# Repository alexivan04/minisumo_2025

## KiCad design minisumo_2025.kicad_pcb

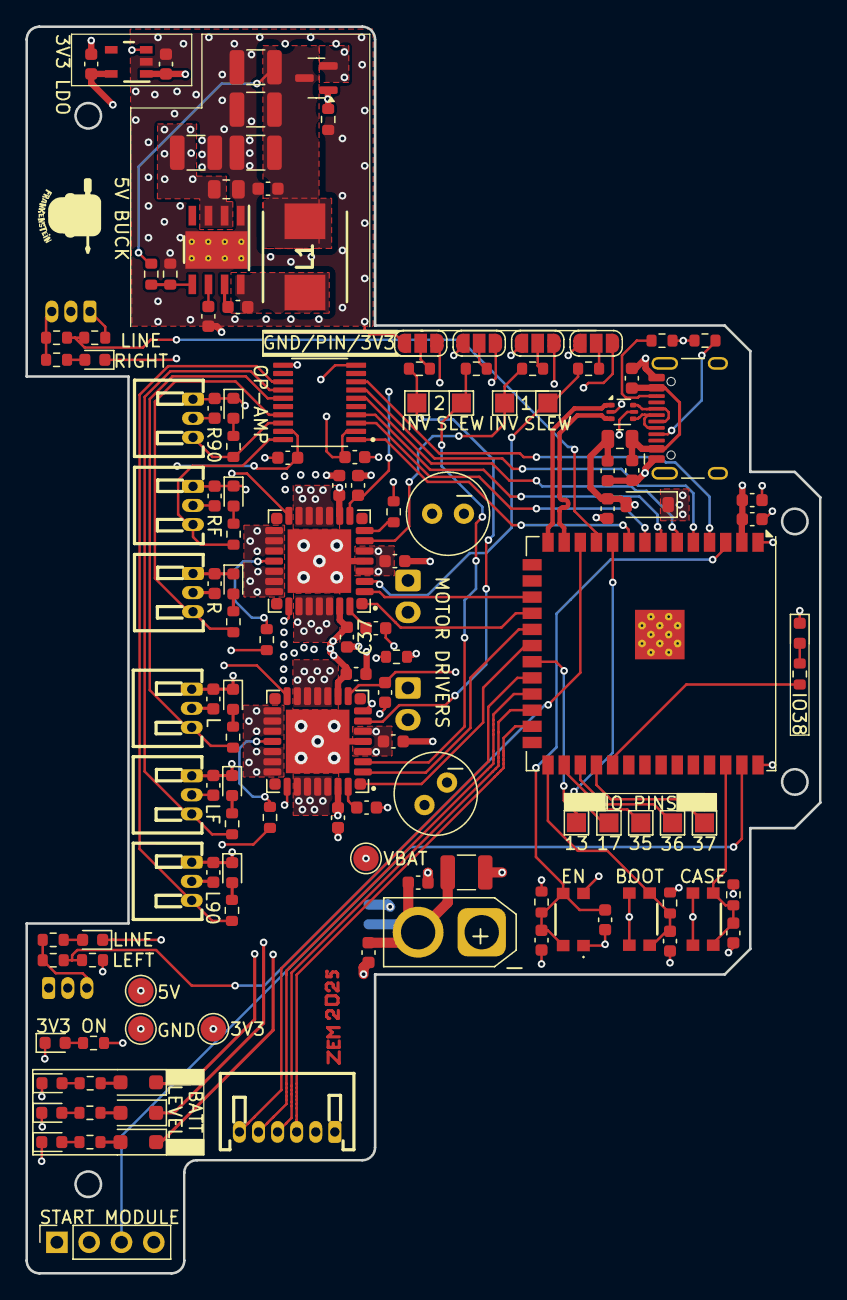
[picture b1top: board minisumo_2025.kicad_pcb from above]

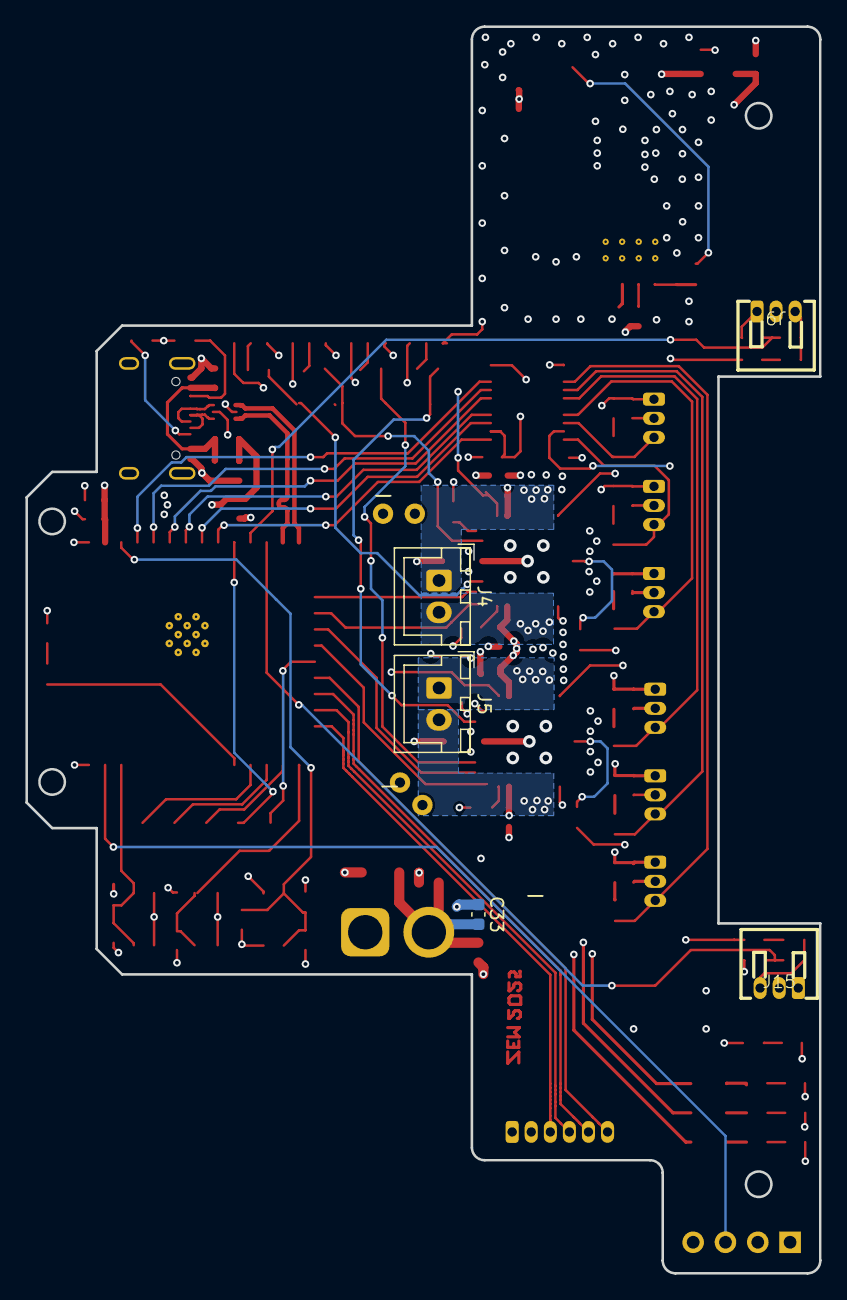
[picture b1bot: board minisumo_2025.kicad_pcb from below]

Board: 4 copper layers, 62.4 x 98.0 mm, 134 parts (5 on the bottom side), 85 nets.

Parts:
C1, C3, C6, C7, C11, C12, C16, C17, C18, C21, C23, C25, C26, C27, C28, C29, C30, C34, C37, C38, C44, C45, C46, C47, C48, C49: 0.1uF; C_0603_1608Metric
C2, C14, C15, C33: 10uF; C_0603_1608Metric
C4: 10uF; C_1210_3225Metric
C5: 220nF; C_0805_2012Metric
C8, C9, C10, C31: 47uF; C_1210_3225Metric
C13, C32, C36: 1uF; C_0603_1608Metric
C19, C20: 33nF; C_0603_1608Metric
C22, C24: 100uF - low ESR; C_Radial_D6.3mm_H11.0mm_P2.50mm
C35: 4.7uF; C_0603_1608Metric
D2, D7, D8, D9: 1.95Vf, 20mA, RED; LED_0603_1608Metric
D3: D_Schottky_Small; D_SOD-123
D4: 10V; D_SOD-123F
D5: 8.2V; D_SOD-123F
D6: 6.2V; D_SOD-123F
D10, D11, D12, D13, D14, D15, D16, D17, D18: LED_Small; LED_0603_1608Metric
FB1: FerriteBead_Small; C_0805_2012Metric
J1: USB_C Connector; USB_C_Receptacle_HCTL_HC-TYPE-C-16P-01A
J3: START_MODULE; PinSocket_1x04_P2.54mm_Vertical
J4: MOTOR1; JST_XH_B2B-XH-A_1x02_P2.50mm_Vertical
J5: MOTOR2; JST_XH_B2B-XH-A_1x02_P2.50mm_Vertical
J6: BATT_IN; AMASS_XT30U-F_1x02_P5.0mm_Vertical
J8: DISTANCE_CENTER; CONN-TH_S6B-ZR-3.4-LF-SN
J9: LINE_RIGHT; CONN-TH_S3B-ZR-3.4-LF-SN
J10: DISTANCE_R90; CONN-TH_S3B-ZR-3.4-LF-SN
J11: DISTANCE_R; CONN-TH_S3B-ZR-3.4-LF-SN
J12: DISTANCE_RF; CONN-TH_S3B-ZR-3.4-LF-SN
J13: DISTANCE_L90; CONN-TH_S3B-ZR-3.4-LF-SN
J14: DISTANCE_L; CONN-TH_S3B-ZR-3.4-LF-SN
J15: LINE_LEFT; CONN-TH_S3B-ZR-3.4-LF-SN
J16: DISTANCE_LF; CONN-TH_S3B-ZR-3.4-LF-SN
JP1, JP2, JP3, JP4: SolderJumper_3_Open; SolderJumper-3_P1.3mm_Open_RoundedPad1.0x1.5mm_NumberLabels
L1: 8.2uH, 21mOhm; INDPM7166X300N
Q1: Si2371EDS; SOT-23
R1, R6, R7, R8, R13, R14, R15, R16, R17, R18, R19, R25: 10k; R_0603_1608Metric
R2, R3: 5k1; R_0603_1608Metric
R4, R33: 100k; R_0603_1608Metric
R5: 24k9; R_0603_1608Metric
R9, R10, R11, R12, R21, R23: 1k; R_0603_1608Metric
R20, R26, R27, R28, R29, R30, R31, R32: 3k3; R_0603_1608Metric
R22, R24: 2k; R_0603_1608Metric
SW1: RESET; 435441019830
SW2: CASE; 435441019830
SW3: BOOT; 435441019830
TP1: GPIO13; TestPoint_Pad_1.5x1.5mm
TP6: SLEW_1; TestPoint_Pad_1.5x1.5mm
TP7: INV_1; TestPoint_Pad_1.5x1.5mm
TP8: GPIO35; TestPoint_Pad_1.5x1.5mm
TP9: GPIO36; TestPoint_Pad_1.5x1.5mm
TP10: SLEW_2; TestPoint_Pad_1.5x1.5mm
TP11: INV_2; TestPoint_Pad_1.5x1.5mm
TP12: GPIO37; TestPoint_Pad_1.5x1.5mm
TP13: GPIO17; TestPoint_Pad_1.5x1.5mm
U1: LMR33630ADDAR; DDA0008J
U2: USBLC6-2P6; SOT-666
U3: ESP32-S3-WROOM-1; ESP32-S3-WROOM-1U
U4: TLV75733PDBVR; DBV0005A_N
U5: TXS0108EPWR; SOP65P640X120-20N
U6, U7: MC33926PNB; QFN80P800X800X220-33N

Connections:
+3V3: C1.1, C2.1, C14.2, C27.1, C28.1, C29.1, J3.1, J8.1, JP1.3 (B), JP2.3 (B), JP3.3 (B), JP4.3 (B), R1.1, R6.1, R7.1, R8.1, R13.1, R15.1, U3.2 (3V3), U4.5 (OUT), U5.2 (VCCA), U5.10 (OE), U6.10 (EN), U6.16 (~D2), U7.10 (EN), U7.16 (~D2)
+5V: C15.2, C30.1, C44.1, C45.1, C46.1, C47.1, C48.1, C49.1, D3.1 (K), J9.2, J10.2, J11.2, J12.2, J13.2, J14.2, J15.2, J16.2, Q1.2 (S), U4.1 (IN), U4.3 (EN), U5.19 (VCCB)
+BATT: C4.1, C5.1, C19.1, C20.1, C21.1, C22.1, C23.1, C24.1, C25.1, C31.2, C33.2, C34.1, C35.2, C36.2, C37.1, C38.1, D4.1 (K), D5.1 (K), D6.1 (K), J6.2, U1.2 (VIN), U1.3 (EN), U6.4 (VPWR), U6.6 (VPWR), U6.11 (VPWR), U6.31 (VPWR), U7.4 (VPWR), U7.6 (VPWR), U7.11 (VPWR), U7.31 (VPWR)
/DRIVERS/CCP_1: C19.2, U6.32 (CCP)
/DRIVERS/CCP_2: C20.2, U7.32 (CCP)
/DRIVERS/INV_1: R11.1, TP7.1, U6.7 (INV)
/DRIVERS/INV_2: R12.1, TP11.1, U7.7 (INV)
/DRIVERS/MOTOR1_A: J4.1, U6.12 (OUT1), U6.13 (OUT1), U6.14 (OUT1), U6.15 (OUT1)
/DRIVERS/MOTOR1_B: J4.2, U6.27 (OUT2), U6.28 (OUT2), U6.29 (OUT2), U6.30 (OUT2)
/DRIVERS/MOTOR2_A: J5.1, U7.12 (OUT1), U7.13 (OUT1), U7.14 (OUT1), U7.15 (OUT1)
/DRIVERS/MOTOR2_B: J5.2, U7.27 (OUT2), U7.28 (OUT2), U7.29 (OUT2), U7.30 (OUT2)
/DRIVERS/SLEW_1: R9.1, TP6.1, U6.3 (SLEW)
/DRIVERS/SLEW_2: R10.1, TP10.1, U7.3 (SLEW)
/POWER/D_N: J1.A7 (D-), J1.B7 (D-), U2.4 (I/O2)
/POWER/D_P: J1.A6 (D+), J1.B6 (D+), U2.6 (I/O1)
/POWER/VBUS: C6.1, C26.1, D3.2 (A), FB1.2, Q1.1 (G), R33.1, U2.5 (VBUS)
/SENSORS/DISTANCE_L90_OUT: J13.3, R28.1, U5.13 (B7)
/SENSORS/DISTANCE_LF_OUT: J16.3, R30.1, U5.14 (B6)
/SENSORS/DISTANCE_L_OUT: J14.3, R29.1, U5.15 (B5)
/SENSORS/DISTANCE_R90_OUT: J10.3, R26.1, U5.18 (B2)
/SENSORS/DISTANCE_RF_OUT: J12.3, R27.1, U5.20 (B1)
/SENSORS/DISTANCE_R_OUT: J11.3, R20.1, U5.17 (B3)
/SENSORS/LINE_LEFT_OUT: J15.3, R23.2, R32.1
/SENSORS/LINE_RIGHT_OUT: J9.3, R21.2, R31.1
CASE: C18.1, R8.2, SW2.2 (D), SW2.3 (C), U3.38 (IO2)
D+: U2.1 (I/O1), U3.14 (USB_D+)
D-: U2.3 (I/O2), U3.13 (USB_D-)
DISTANCE_INTR: J8.6, U3.22 (IO14)
DISTANCE_L: U3.6 (IO6), U5.6 (A5)
DISTANCE_L90: U3.4 (IO4), U5.8 (A7)
DISTANCE_LF: U3.5 (IO5), U5.7 (A6)
DISTANCE_R: U3.7 (IO7), U5.4 (A3)
DISTANCE_R90: U3.8 (IO15), U5.3 (A2)
DISTANCE_RF: U3.9 (IO16), U5.1 (A1)
ESP_BOOT: C12.2, R7.2, SW3.2 (D), SW3.3 (C), U3.27 (IO0)
ESP_EN: C7.2, C32.2, R1.2, SW1.2 (D), SW1.3 (C), U3.3 (EN)
GND: C1.2, C2.2, C4.2, C5.2, C6.2, C7.1, C8.1, C9.1, C10.1, C11.1, C12.1, C13.2, C14.1, C15.1, C16.2, C17.2, C18.2, C21.2, C22.2, C23.2, C24.2, C25.2, C26.2, C27.2, C28.2, C29.2, C30.2, C31.1, C32.1, C33.1, C34.2, C35.1, C36.1, C37.2, C38.2, C44.2, C45.2, C46.2, C47.2, C48.2, C49.2, D2.1 (K), D7.1 (K), D8.1 (K), D9.1 (K), D10.1 (K), D11.1 (K), D12.1 (K), D13.1 (K), D14.1 (K), D15.1 (K), D16.1 (K), D17.1 (K), D18.1 (K), J1.A1 (GND), J1.A12 (GND), J1.B1 (GND), J1.B12 (GND), J3.2, J6.1, J8.2, J9.1, J10.1, J11.1, J12.1, J13.1, J14.1, J15.1, J16.1, JP1.1 (A), JP2.1 (A), JP3.1 (A), JP4.1 (A), R2.1, R3.1, R5.1, R14.1, R16.1, R22.1, R24.1, R33.2, SW1.1 (C), SW1.4 (C), SW2.1 (C), SW2.4 (C), SW3.1 (C), SW3.4 (C), U1.1 (PGND), U1.9 (AGND), U1.V, U2.2 (GND), U3.1 (GND), U3.40 (GND), U3.41 (GND), U4.2 (GND), U5.11 (GND), U6.5 (AGND), U6.18 (PGND), U6.19 (PGND), U6.20 (PGND), U6.22 (PGND), U6.23 (PGND), U6.24 (PGND), U6.26 (D1), U6.33 (AGND), U7.5 (AGND), U7.18 (PGND), U7.19 (PGND), U7.20 (PGND), U7.22 (PGND), U7.23 (PGND), U7.24 (PGND), U7.26 (D1), U7.33 (AGND)
GPIO1: J3.3, U3.39 (IO1)
GPIO8: R23.1, R24.2, U3.12 (IO8)
GPIO9: U3.17 (IO9), U6.2 (IN1)
GPIO10: U3.18 (IO10), U6.1 (IN2)
GPIO11: U3.19 (IO11), U7.2 (IN1)
GPIO12: U3.20 (IO12), U7.1 (IN2)
GPIO13: TP1.1, U3.21 (IO13)
GPIO17: TP13.1, U3.10 (IO17)
GPIO18: R21.1, R22.2, U3.11 (IO18)
GPIO21: J8.5, U3.23 (IO21)
GPIO35: TP8.1, U3.28 (IO35)
GPIO36: TP9.1, U3.29 (IO36)
GPIO37: TP12.1, U3.30 (IO37)
GPIO38: R19.1, U3.31 (IO38)
GPIO47: J8.4, U3.24 (IO47)
GPIO48: J8.3, U3.25 (IO48)
unnamed: C16.1, C17.1, FB1.1, J1.A4 (VBUS), J1.A9 (VBUS), J1.B4 (VBUS), J1.B9 (VBUS)
unnamed: D2.2 (A), R6.2
unnamed: D4.2 (A), R17.1
unnamed: D5.2 (A), R18.1
unnamed: D6.2 (A), R25.1
unnamed: D7.2 (A), R17.2
unnamed: D8.2 (A), R18.2
unnamed: D9.2 (A), R25.2
unnamed: D10.2 (A), R19.2
unnamed: D11.2 (A), R20.2
unnamed: D12.2 (A), R26.2
unnamed: D13.2 (A), R27.2
unnamed: D14.2 (A), R28.2
unnamed: D15.2 (A), R29.2
unnamed: D16.2 (A), R30.2
unnamed: D17.2 (A), R31.2
unnamed: D18.2 (A), R32.2
unnamed: J1.A5 (CC1), R2.2
unnamed: J1.B5 (CC2), R3.2
unnamed: JP1.2 (C), R9.2
unnamed: JP2.2 (C), R10.2
unnamed: JP3.2 (C), R11.2
unnamed: JP4.2 (C), R12.2
unnamed: C8.2, C9.2, C10.2, C11.2, L1.2, Q1.3 (D), R4.2
unnamed: C3.2, U1.7 (BOOT)
unnamed: R4.1, R5.2, U1.5 (FB)
unnamed: C3.1, L1.1, U1.8 (SW)
unnamed: C13.1, U1.6 (VCC)
unnamed: R14.2, U6.8 (FB)
unnamed: R13.2, U6.21 (~SF)
unnamed: R16.2, U7.8 (FB)
unnamed: R15.2, U7.21 (~SF)

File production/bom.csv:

Designator,Footprint,Quantity,Value,LCSC Part #
"C1, C12, C16, C17, C18, C26, C29, C3, C30, C6, C7",0603,11,0.1uF,C1525
"C10, C31, C8, C9",1210,4,47uF,C77101
"C11, C21, C23, C25, C27, C28, C34, C37, C38",0603,9,0.1uF,C77050
"C13, C36",0603,2,1uF,C92759
"C14, C15, C33",0603,3,10uF,C437568
"C19, C20",0603,2,33nF,C1614
C2,0603,1,10uF,C70225
"C22, C24",C_Radial_D6.3mm_H11.0mm_P2.50mm,2,100uF - low ESR,
C32,0603,1,1uF,C14445
C35,0603,1,4.7uF,C437568
C4,1210,1,10uF,C437568
"C44, C45, C46, C47, C48, C49",0603,6,0.1uF,C437568
C5,0805,1,220nF,C1770
D10,0603,1,LED_Small,C2286
"D11, D12, D13, D14, D15, D16, D17, D18",0603,8,LED_Small,
"D2, D7, D8, D9",0603,4,"1.95Vf, 20mA, RED",C2286
D3,D_SOD-123,1,D_Schottky_Small,
D4,D_SOD-123F,1,10V,C173431
D5,D_SOD-123F,1,8.2V,C19077406
D6,D_SOD-123F,1,6.2V,C115277
FB1,0805,1,FerriteBead_Small,
J1,USB_C_Receptacle_HCTL_HC-TYPE-C-16P-01A,1,USB_C Connector,C165948
J10,CONN-TH_S3B-ZR-3.4-LF-SN,1,DISTANCE_R90,
J11,CONN-TH_S3B-ZR-3.4-LF-SN,1,DISTANCE_R,
J12,CONN-TH_S3B-ZR-3.4-LF-SN,1,DISTANCE_RF,
J13,CONN-TH_S3B-ZR-3.4-LF-SN,1,DISTANCE_L90,
J14,CONN-TH_S3B-ZR-3.4-LF-SN,1,DISTANCE_L,
J15,CONN-TH_S3B-ZR-3.4-LF-SN,1,LINE_LEFT,
J16,CONN-TH_S3B-ZR-3.4-LF-SN,1,DISTANCE_LF,
J3,PinSocket_1x04_P2.54mm_Vertical,1,START_MODULE,
J4,JST_XH_B2B-XH-A_1x02_P2.50mm_Vertical,1,MOTOR1,
J5,JST_XH_B2B-XH-A_1x02_P2.50mm_Vertical,1,MOTOR2,
J6,AMASS_XT30U-F_1x02_P5.0mm_Vertical,1,BATT_IN,
J8,CONN-TH_S6B-ZR-3.4-LF-SN,1,DISTANCE_CENTER,
J9,CONN-TH_S3B-ZR-3.4-LF-SN,1,LINE_RIGHT,
L1,INDPM7166X300N,1,"8.2uH, 21mOhm",C5329540
Q1,SOT-23,1,Si2371EDS,
"R1, R13, R14, R15, R16, R7",0603,6,10k,C25531
"R10, R11, R12, R9",0603,4,1k,C11702
R17,0603,1,10k,C25112
R18,0603,1,10k,C25102
"R19, R6",0603,2,10k,C25131
"R2, R3",0603,2,5k1,C25905
"R20, R26, R27, R28, R29, R30, R31, R32",0603,8,3k3,C25131
"R21, R23",0603,2,1k,C4109
"R22, R24",0603,2,2k,C25890
R25,0603,1,10k,C25087
R33,0603,1,100k,C25102
R4,0603,1,100k,C481918
R5,0603,1,24k9,C844504
R8,0603,1,10k,C477765
SW1,435441019830,1,RESET,C720477
SW2,435441019830,1,CASE,C720477
SW3,435441019830,1,BOOT,C720477
TP1,TestPoint_Pad_1.5x1.5mm,1,GPIO13,
TP10,TestPoint_Pad_1.5x1.5mm,1,SLEW_2,
TP11,TestPoint_Pad_1.5x1.5mm,1,INV_2,
TP12,TestPoint_Pad_1.5x1.5mm,1,GPIO37,
TP13,TestPoint_Pad_1.5x1.5mm,1,GPIO17,
TP6,TestPoint_Pad_1.5x1.5mm,1,SLEW_1,
TP7,TestPoint_Pad_1.5x1.5mm,1,INV_1,
TP8,TestPoint_Pad_1.5x1.5mm,1,GPIO35,
TP9,TestPoint_Pad_1.5x1.5mm,1,GPIO36,
U1,DDA0008J,1,LMR33630ADDAR,C841384
U2,SOT-666,1,USBLC6-2P6,C15999
U3,ESP32-S3-WROOM-1U,1,ESP32-S3-WROOM-1,C701341
U4,DBV0005A_N,1,TLV75733PDBVR,C485517
U5,SOP65P640X120-20N,1,TXS0108EPWR,
"U6, U7",QFN80P800X800X220-33N,2,MC33926PNB,C1556870

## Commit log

2025-02-13 basic buttons
2025-02-13 added usb-c connector
2025-02-15 added power circuitry
2025-02-15 added base for motor driver
2025-02-15 modified power circuitry
2025-02-16 finished drivers, added distance sensors with level shifter
2025-02-16 changed level shifter and added line sensors
2025-02-17 started layout
2025-02-17 added connectors and 3D models
2025-02-17 added JST connector
2025-02-18 base layout
2025-02-18 regulator routing
2025-02-18 minor adjustment
2025-02-18 motor driver traces
2025-02-18 more driver traces
2025-02-19 more routing
2025-02-20 driver routing
2025-02-20 driver layout done
2025-02-20 final driver routing and layout
2025-02-20 routing
2025-02-20 usb routing
2025-02-20 finished overall routing
2025-02-21 added leds for power
2025-02-24 finished layout
2025-02-24 silkscreen
2025-02-25 backup
2025-02-25 final.
2025-04-01 saved required changes
2025-04-01 more
2025-04-08 test board layout
2025-04-08 more testing
2025-04-08 another variant
2025-04-08 final test layout
2025-04-10 backup with layout
2025-04-13 layout done
2025-04-14 more changes
2025-04-14 final layout
2025-04-15 silksreen and bom
2025-04-16 testing
2025-04-16 added global labels
2025-04-16 removed file
2025-04-16 added PDFs
2025-04-19 added test pads and gate resistor for PMOS
2025-05-07 custom
2025-05-11 added code
2026-04-22 2026 version
